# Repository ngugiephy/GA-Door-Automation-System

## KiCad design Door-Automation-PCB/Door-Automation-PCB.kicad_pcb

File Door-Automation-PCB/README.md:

# Door Automation PCB

This PCB design was done using Kicad.

If you don't have Kicad installed on your system,you can download and install it from [here](https://www.kicad.org/download/).

You can checkout some Kicad documentation to get started [here](https://docs.kicad.org/).

## Schematic

The pdf version of the schematic is available in the schematic subfolder.

## PCB

The final PCB looks like this without components

It looks like this with components

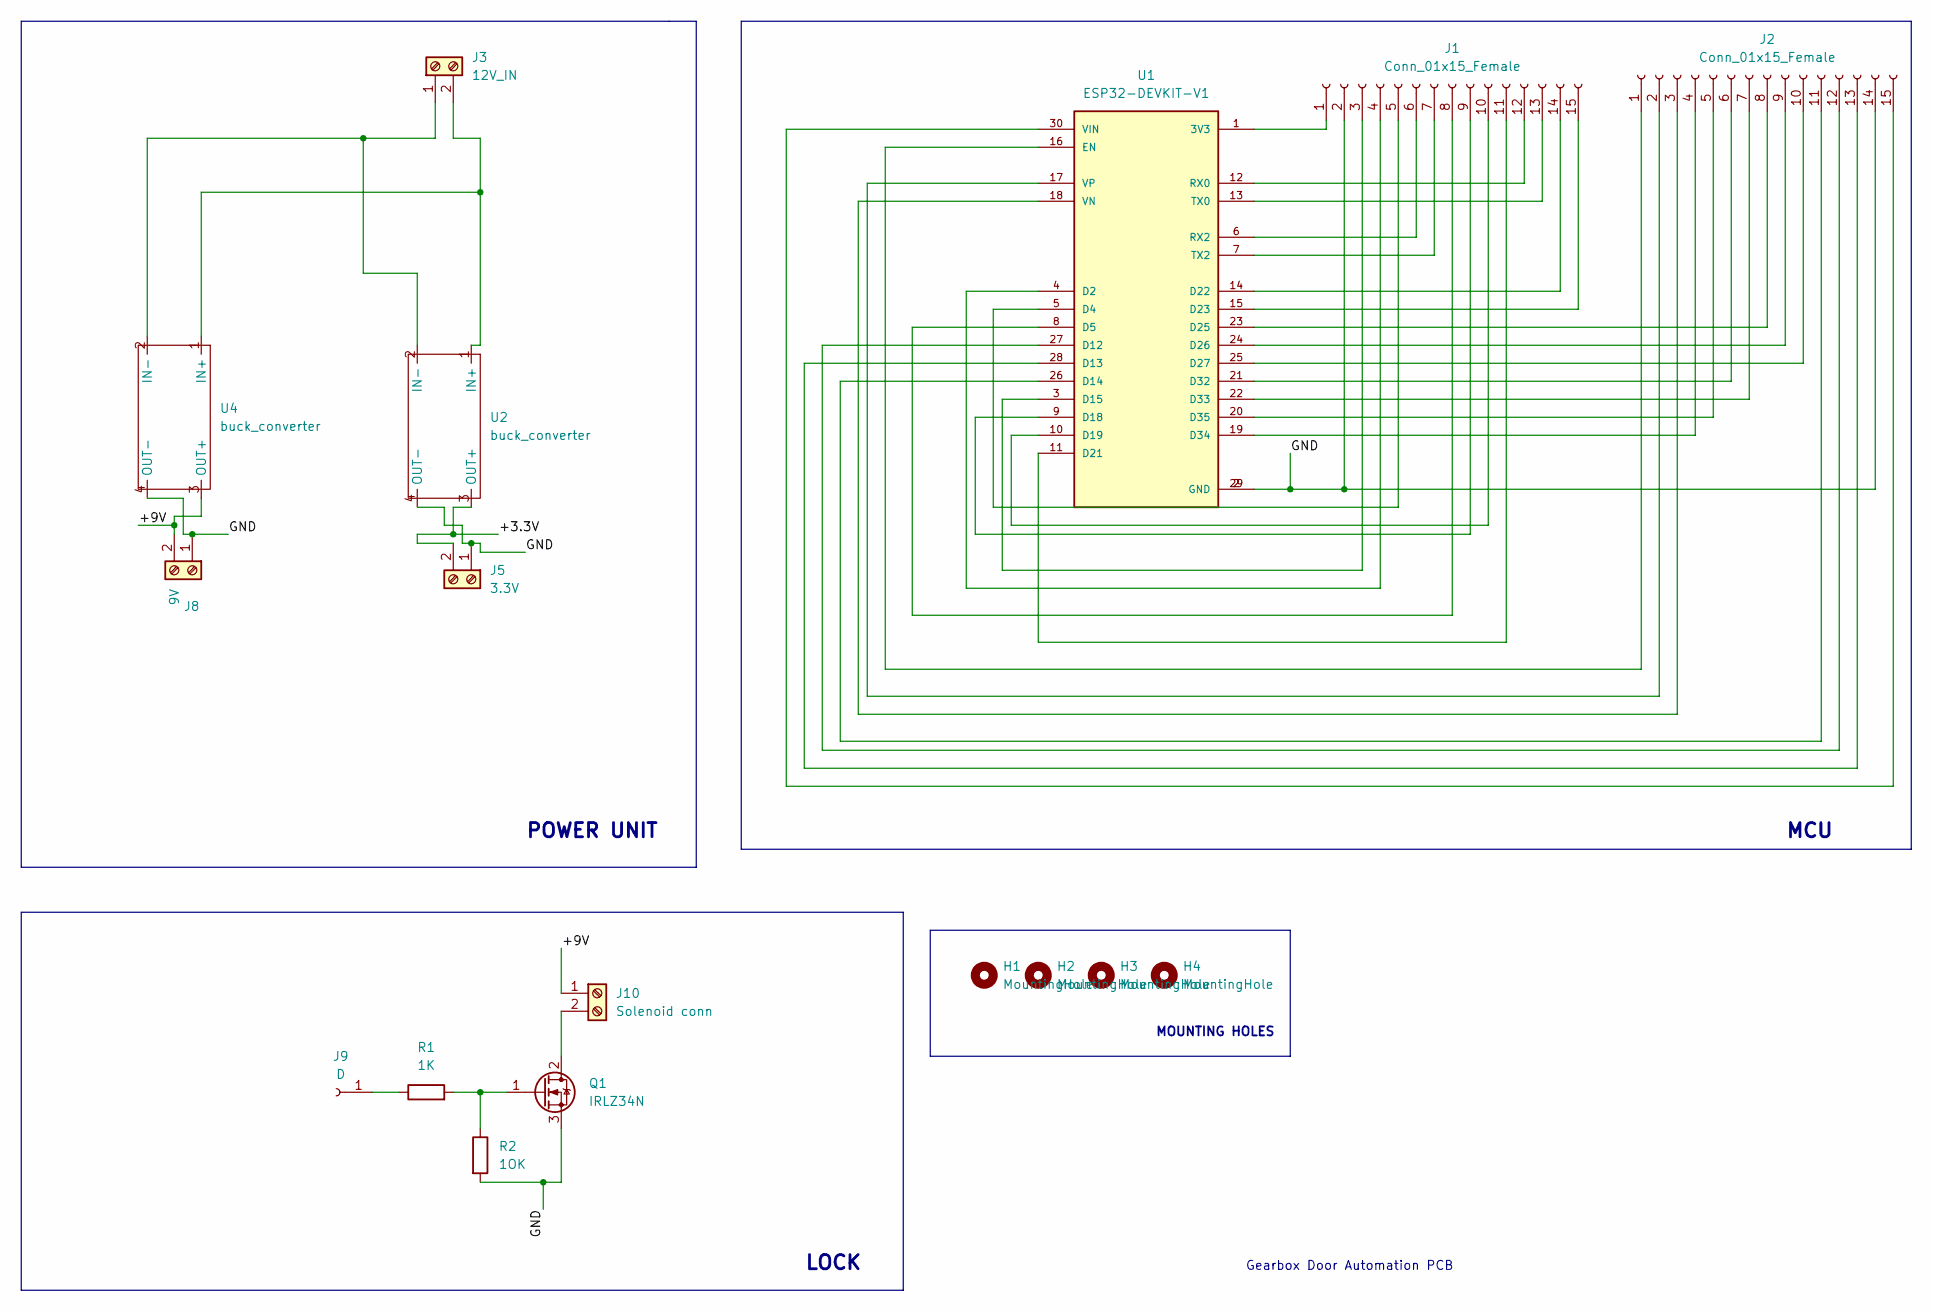
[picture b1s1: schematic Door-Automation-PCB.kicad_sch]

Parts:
H1, H2, H3, H4: MountingHole; MountingHole_2.5mm
J1, J2: Conn_01x15_Female; PinSocket_1x15_P2.54mm_Vertical
J3: 12V_IN; TerminalBlock_Phoenix_MKDS-1,5-2-5.08_1x02_P5.08mm_Horizont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
J5: 3.3V; TerminalBlock_Phoenix_MKDS-1,5-2-5.08_1x02_P5.08mm_Horizont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
J8: 9V; TerminalBlock_Phoenix_MKDS-1,5-2-5.08_1x02_P5.08mm_Horizont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
J9: D; PinSocket_1x01_P2.00mm_Vertical
J10: Solenoid conn; TerminalBlock_Phoenix_MKDS-1,5-2-5.08_1x02_P5.08mm_Horizont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
Q1: IRLZ34N; TO-220-3_Vertical
R1: 1K; R_Axial_DIN0204_L3.6mm_D1.6mm_P7.62mm_Horizontal
R2: 1OK; R_Axial_DIN0204_L3.6mm_D1.6mm_P7.62mm_Horizontal
U1: ESP32-DEVKIT-V1; MODULE_ESP32_DEVKIT_V1; PARTREV N/A
U2, U4: buck_converter

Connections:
/+3.3V: J5.2, U2.3 (OUT+)
/+9V: J8.2, J10.1, U4.3 (OUT+)
/GND: J1.2, J2.14, J5.1, J8.1, Q1.3 (S), R2.2, U1.2 (GND), U1.29 (GND), U2.4 (OUT-), U4.4 (OUT-)
unnamed: J1.1, U1.1 (3V3)
unnamed: J1.3, U1.3 (D15)
unnamed: J1.4, U1.4 (D2)
unnamed: J1.5, U1.5 (D4)
unnamed: J1.6, U1.6 (RX2)
unnamed: J1.7, U1.7 (TX2)
unnamed: J1.8, U1.8 (D5)
unnamed: J1.9, U1.9 (D18)
unnamed: J1.10, U1.10 (D19)
unnamed: J1.11, U1.11 (D21)
unnamed: J1.12, U1.12 (RX0)
unnamed: J1.13, U1.13 (TX0)
unnamed: J1.14, U1.14 (D22)
unnamed: J1.15, U1.15 (D23)
unnamed: J2.1, U1.16 (EN)
unnamed: J2.2, U1.17 (VP)
unnamed: J2.3, U1.18 (VN)
unnamed: J2.4, U1.19 (D34)
unnamed: J2.5, U1.20 (D35)
unnamed: J2.6, U1.21 (D32)
unnamed: J2.7, U1.22 (D33)
unnamed: J2.8, U1.23 (D25)
unnamed: J2.9, U1.24 (D26)
unnamed: J2.10, U1.25 (D27)
unnamed: J2.11, U1.26 (D14)
unnamed: J2.12, U1.27 (D12)
unnamed: J2.13, U1.28 (D13)
unnamed: J2.15, U1.30 (VIN)
unnamed: J3.1, U2.2 (IN-), U4.2 (IN-)
unnamed: J3.2, U2.1 (IN+), U4.1 (IN+)
unnamed 33: J9.1, R1.1; also elsewhere on the board
unnamed: J10.2, Q1.2 (D)
unnamed: Q1.1 (G), R1.2, R2.1

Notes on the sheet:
MCU
Gearbox Door Automation PCB
MOUNTING HOLES
LOCK
POWER UNIT

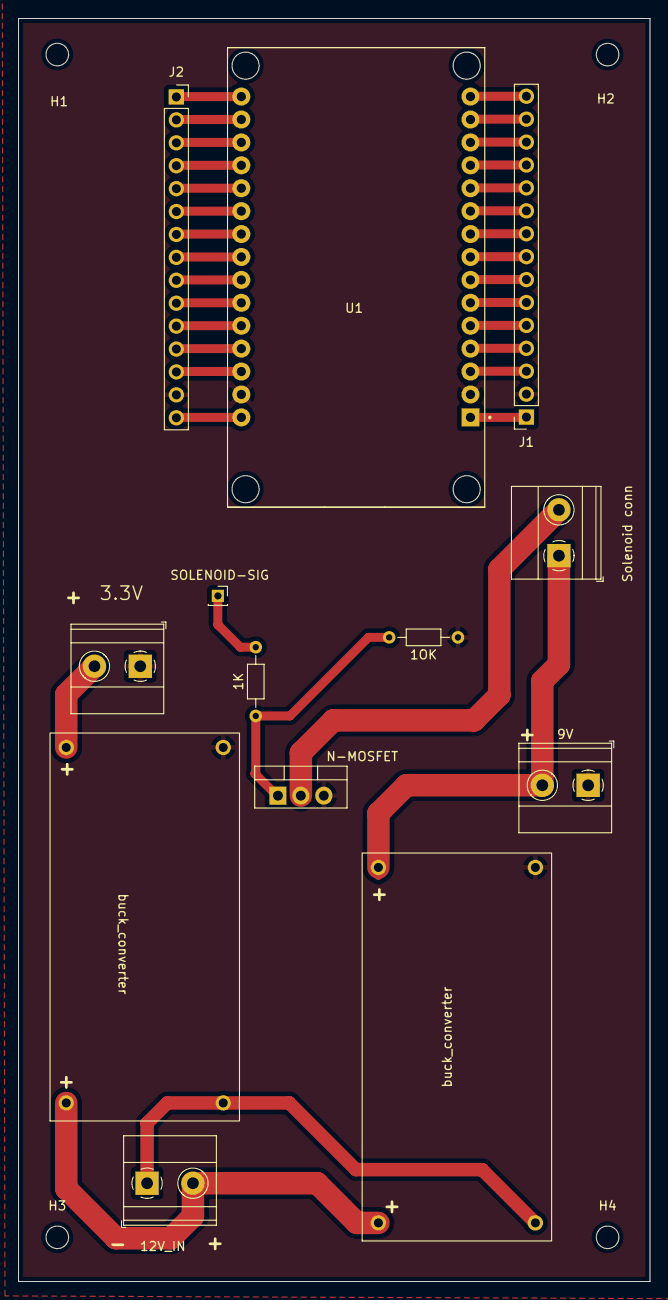
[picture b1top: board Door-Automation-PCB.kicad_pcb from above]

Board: 2 copper layers, 70.0 x 140.0 mm, 17 parts (0 on the bottom side), 36 nets.

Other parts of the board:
SOLENOID-SIG: D; PinSocket_1x01_P2.00mm_Vertical

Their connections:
unnamed 33: SOLENOID-SIG.1; also elsewhere on the board

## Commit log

2022-05-21 This is the addition of a prototype rfid access
2022-06-27 Added imageapp as a submodule
2022-06-27 Updated imageapp README.md file
2022-06-28 Addition of face detection and face recognition model and software
2022-06-28 Made ML folder
2022-06-28 basic setup
2022-06-28 Addition of README file and folder
2022-06-28 rfid + keypad
2022-06-29 Modified the face recognition and detection code
2022-06-30 postman boilerplate
2022-06-30 Removed submodule configuration
2022-06-30 Added imageapp correctly
2022-06-30 Modified README.md file
2022-07-08 connect esp to server
2022-07-20 Added mqtt_test folder for simple mqtt test
2022-07-20 Moved db part to db_part folder
2022-07-21 Addition of CNN model and features
2022-07-25 schematic and pcb
2022-07-26 addition of labels and features
2022-07-27 added mosfet switch
2022-07-27 buck converter
2022-07-27 added drill holes
2022-07-28 routed and added readme
2022-08-01 modified README.md
2022-08-03 added copper pour
2022-08-11 added file
